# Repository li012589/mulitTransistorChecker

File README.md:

# mulitTransistorChecker
A open hardware for multi-transistor checker, that is to check a transistor is work or not

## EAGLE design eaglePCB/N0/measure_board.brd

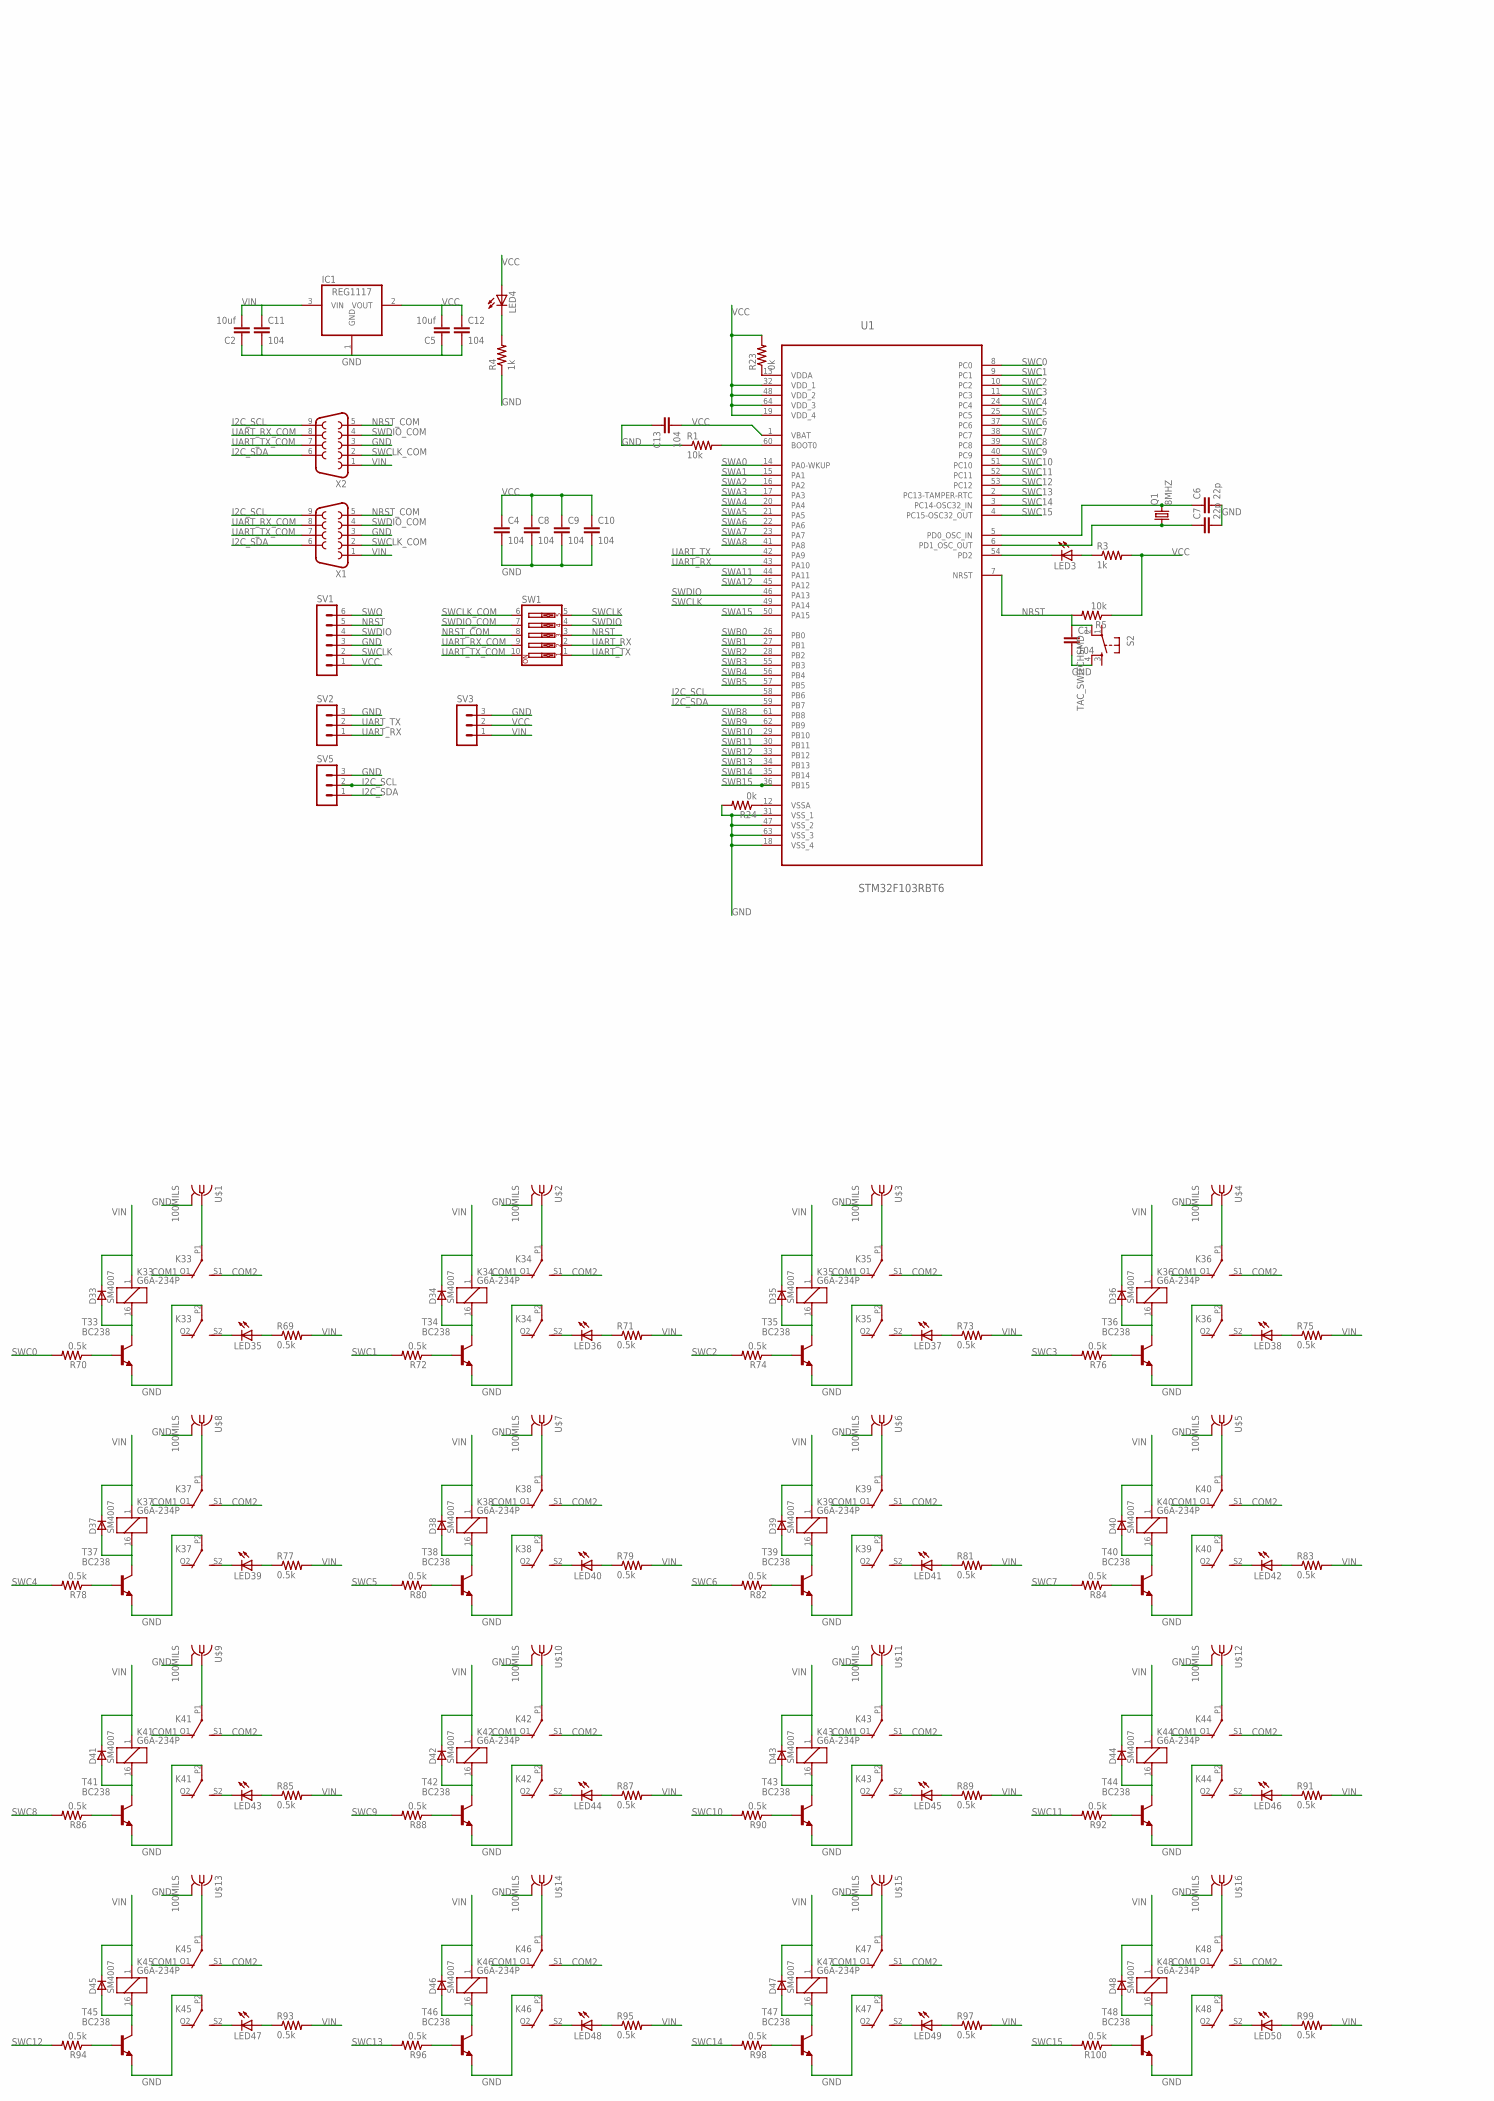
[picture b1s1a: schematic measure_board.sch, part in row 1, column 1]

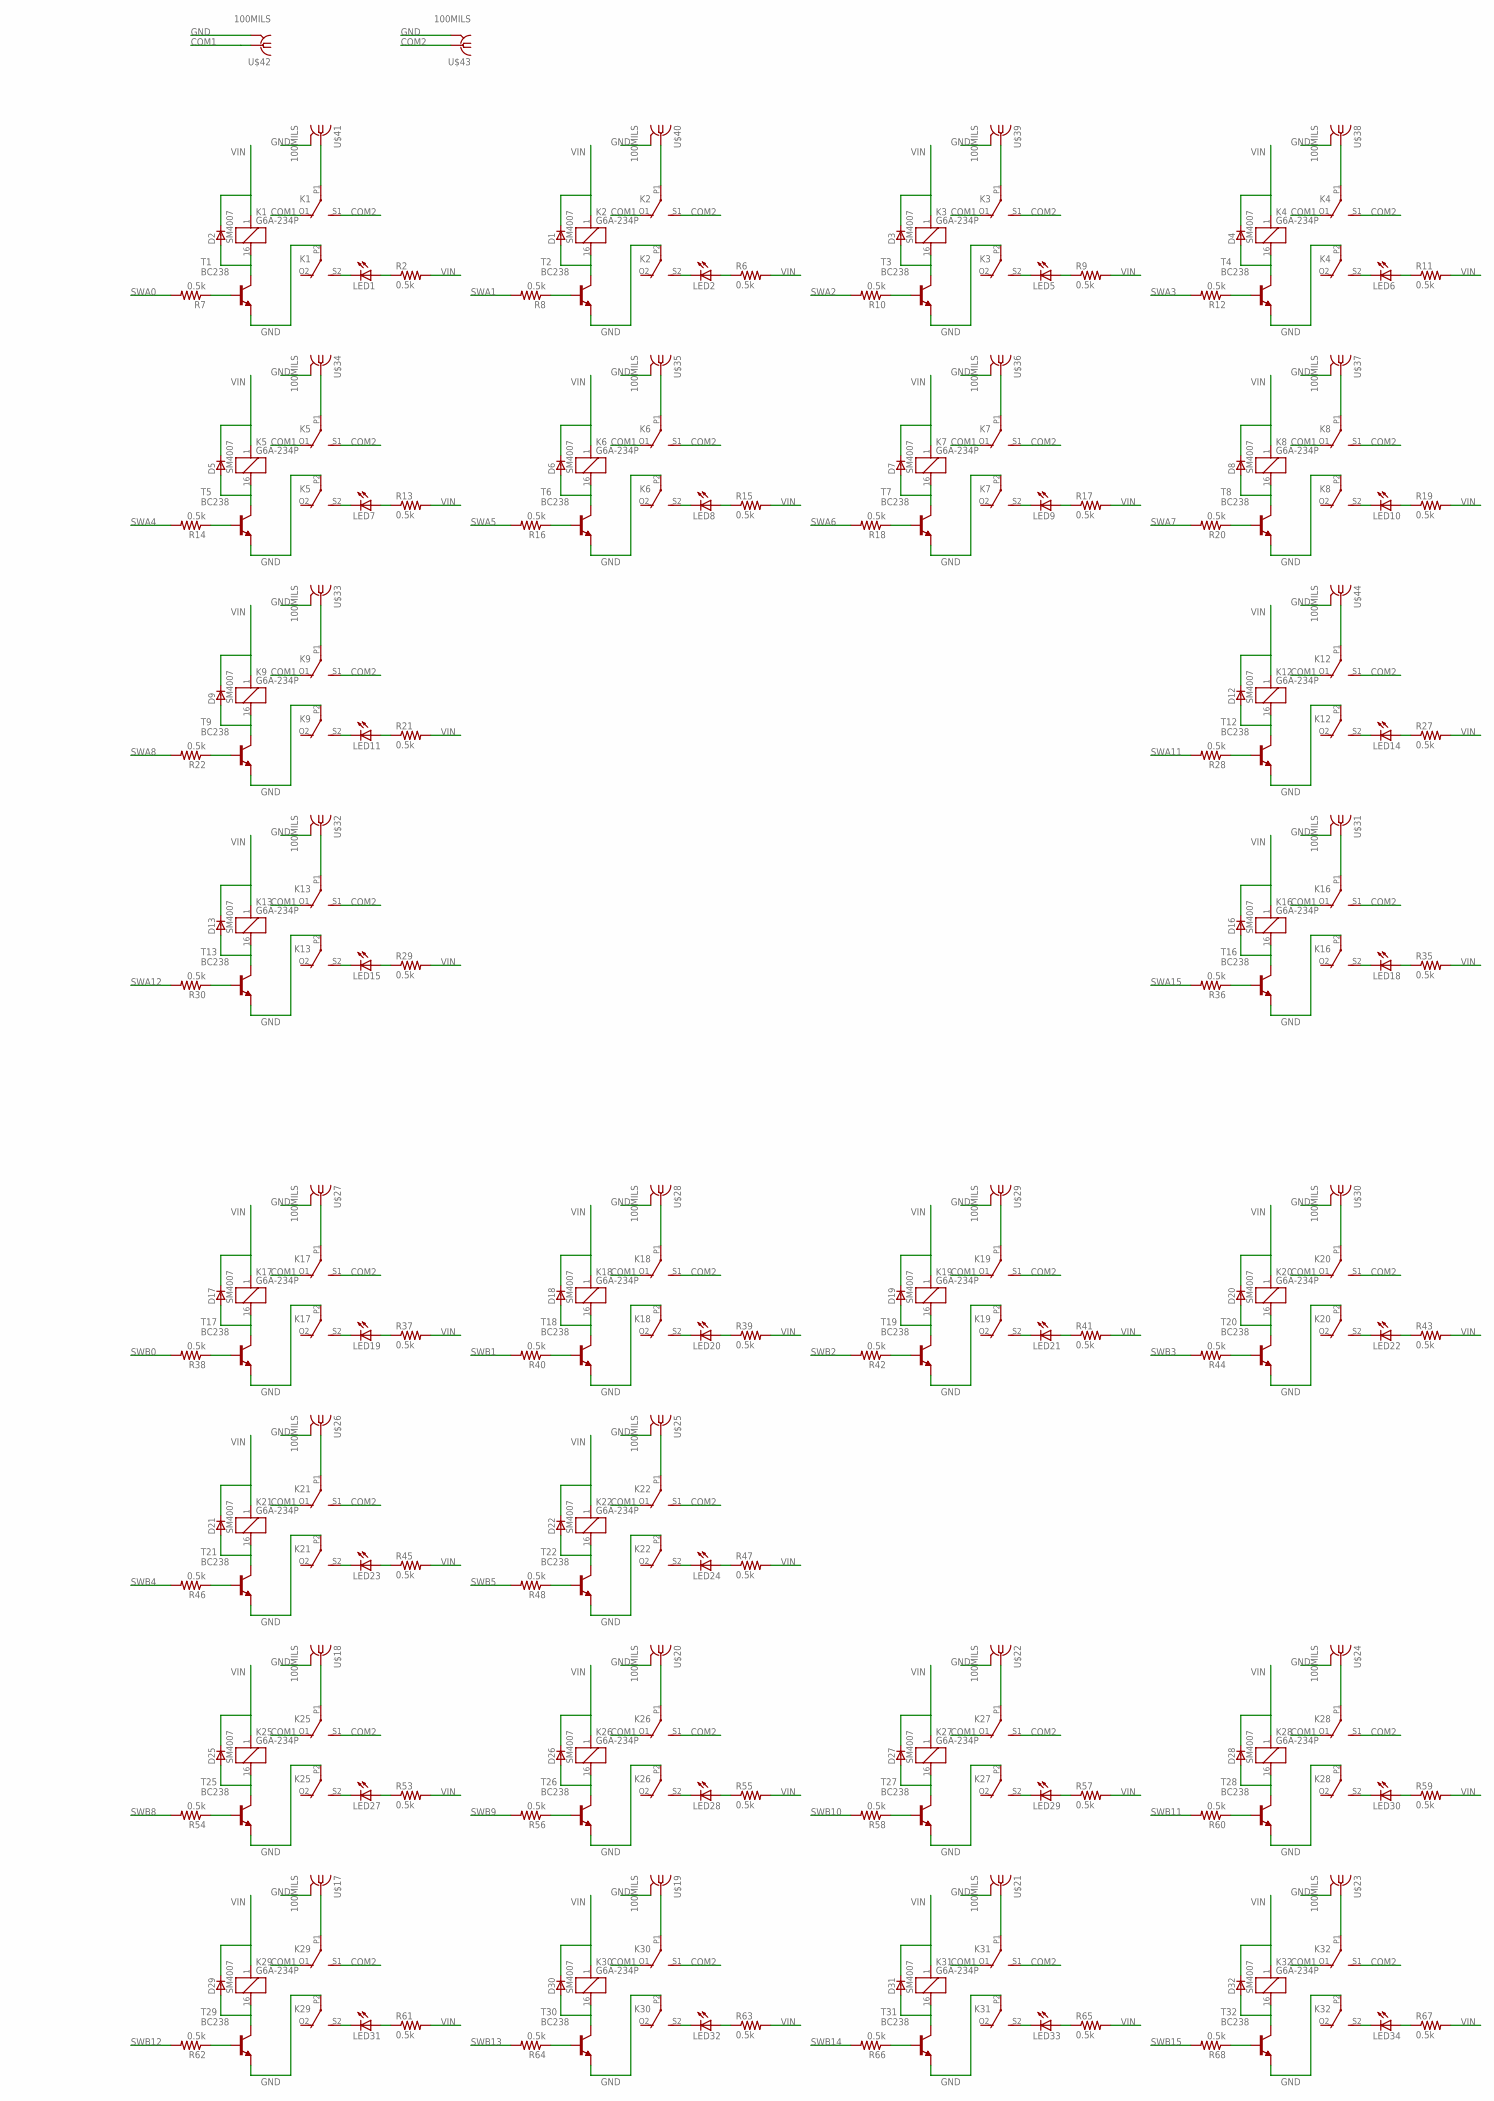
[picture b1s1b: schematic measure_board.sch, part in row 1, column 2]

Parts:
C1, C4, C8, C9, C10, C11, C12, C13: 104; C0805
C2, C5: 10uf; C1206
C6, C7: 22p; C0805
D1, D2, D3, D4, D5, D6, D7, D8, D9, D12, D13, D16, D17, D18, D19, D20, D21, D22, D25, D26, D27, D28, D29, D30, D31, D32, D33, D34, D35, D36, D37, D38, D39, D40, D41, D42, D43, D44, D45, D46, D47, D48: SM4007; MELF-MLL41_DO213AB
IC1: REG1117; SOT223
K1, K2, K3, K4, K5, K6, K7, K8, K9, K12, K13, K16, K17, K18, K19, K20, K21, K22, K25, K26, K27, K28, K29, K30, K31, K32, K33, K34, K35, K36, K37, K38, K39, K40, K41, K42, K43, K44, K45, K46, K47, K48: G6A-234P
LED1, LED2, LED5, LED6, LED7, LED8, LED9, LED10, LED11, LED14, LED15, LED18, LED19, LED20, LED21, LED22, LED23, LED24, LED27, LED28, LED29, LED30, LED31, LED32, LED33, LED34, LED35, LED36, LED37, LED38, LED39, LED40, LED41, LED42, LED43, LED44, LED45, LED46, LED47, LED48, LED49, LED50: LED3MM
LED3, LED4: LEDSML0805; SML0805
Q1: 8MHZ; HC49U70
R1, R5: 10k; M0805
R2, R6, R7, R8, R9, R10, R11, R12, R13, R14, R15, R16, R17, R18, R19, R20, R21, R22, R27, R28, R29, R30, R35, R36, R37, R38, R39, R40, R41, R42, R43, R44, R45, R46, R47, R48, R53, R54, R55, R56, R57, R58, R59, R60, R61, R62, R63, R64, R65, R66, R67, R68, R69, R70, R71, R72, R73, R74, R75, R76, R77, R78, R79, R80, R81, R82, R83, R84, R85, R86, R87, R88, R89, R90, R91, R92, R93, R94, R95, R96, R97, R98, R99, R100: 0.5k; M0805
R3, R4: 1k; M0805
R23, R24: 0k; M0805
S2: TAC_SWITCHSMD; TACTILE-SWITCH-SMD
SV1: MA06-1
SV2, SV3, SV5: MA03-1
SW1: SW_DIP-5; EDG-05
T1, T2, T3, T4, T5, T6, T7, T8, T9, T12, T13, T16, T17, T18, T19, T20, T21, T22, T25, T26, T27, T28, T29, T30, T31, T32, T33, T34, T35, T36, T37, T38, T39, T40, T41, T42, T43, T44, T45, T46, T47, T48: BC238; TO92
U1: STM32F103RBT6; QFP50P1200X1200X160-64N
U$1, U$2, U$3, U$4, U$5, U$6, U$7, U$8, U$9, U$10, U$11, U$12, U$13, U$14, U$15, U$16, U$17, U$18, U$19, U$20, U$21, U$22, U$23, U$24, U$25, U$26, U$27, U$28, U$29, U$30, U$31, U$32, U$33, U$34, U$35, U$36, U$37, U$38, U$39, U$40, U$41, U$42, U$43, U$44: 100MILS; 100MIL
X1, X2: F09HP

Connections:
COM1: K1.O1 (O), K2.O1 (O), K3.O1 (O), K4.O1 (O), K5.O1 (O), K6.O1 (O), K7.O1 (O), K8.O1 (O), K9.O1 (O), K12.O1 (O), K13.O1 (O), K16.O1 (O), K17.O1 (O), K18.O1 (O), K19.O1 (O), K20.O1 (O), K21.O1 (O), K22.O1 (O), K25.O1 (O), K26.O1 (O), K27.O1 (O), K28.O1 (O), K29.O1 (O), K30.O1 (O), K31.O1 (O), K32.O1 (O), K33.O1 (O), K34.O1 (O), K35.O1 (O), K36.O1 (O), K37.O1 (O), K38.O1 (O), K39.O1 (O), K40.O1 (O), K41.O1 (O), K42.O1 (O), K43.O1 (O), K44.O1 (O), K45.O1 (O), K46.O1 (O), K47.O1 (O), K48.O1 (O), U$42.P$1 (1)
COM2: K1.S1 (S), K2.S1 (S), K3.S1 (S), K4.S1 (S), K5.S1 (S), K6.S1 (S), K7.S1 (S), K8.S1 (S), K9.S1 (S), K12.S1 (S), K13.S1 (S), K16.S1 (S), K17.S1 (S), K18.S1 (S), K19.S1 (S), K20.S1 (S), K21.S1 (S), K22.S1 (S), K25.S1 (S), K26.S1 (S), K27.S1 (S), K28.S1 (S), K29.S1 (S), K30.S1 (S), K31.S1 (S), K32.S1 (S), K33.S1 (S), K34.S1 (S), K35.S1 (S), K36.S1 (S), K37.S1 (S), K38.S1 (S), K39.S1 (S), K40.S1 (S), K41.S1 (S), K42.S1 (S), K43.S1 (S), K44.S1 (S), K45.S1 (S), K46.S1 (S), K47.S1 (S), K48.S1 (S), U$43.P$1 (1)
GND: C1.2, C2.1, C4.2, C5.1, C6.2, C7.2, C8.2, C9.2, C10.2, C11.2, C12.2, C13.1, IC1.1 (GND), K1.P2, K2.P2, K3.P2, K4.P2, K5.P2, K6.P2, K7.P2, K8.P2, K9.P2, K12.P2, K13.P2, K16.P2, K17.P2, K18.P2, K19.P2, K20.P2, K21.P2, K22.P2, K25.P2, K26.P2, K27.P2, K28.P2, K29.P2, K30.P2, K31.P2, K32.P2, K33.P2, K34.P2, K35.P2, K36.P2, K37.P2, K38.P2, K39.P2, K40.P2, K41.P2, K42.P2, K43.P2, K44.P2, K45.P2, K46.P2, K47.P2, K48.P2, R1.1, R4.1, R24.2, S2.4, SV1.3, SV2.3, SV3.3, SV5.3, T1.1 (E), T2.1 (E), T3.1 (E), T4.1 (E), T5.1 (E), T6.1 (E), T7.1 (E), T8.1 (E), T9.1 (E), T12.1 (E), T13.1 (E), T16.1 (E), T17.1 (E), T18.1 (E), T19.1 (E), T20.1 (E), T21.1 (E), T22.1 (E), T25.1 (E), T26.1 (E), T27.1 (E), T28.1 (E), T29.1 (E), T30.1 (E), T31.1 (E), T32.1 (E), T33.1 (E), T34.1 (E), T35.1 (E), T36.1 (E), T37.1 (E), T38.1 (E), T39.1 (E), T40.1 (E), T41.1 (E), T42.1 (E), T43.1 (E), T44.1 (E), T45.1 (E), T46.1 (E), T47.1 (E), T48.1 (E), U1.18 (VSS_4), U1.31 (VSS_1), U1.47 (VSS_2), U1.63 (VSS_3), U$1.P$2 (GND), U$1.P$3 (GND), U$1.P$4 (GND), U$1.P$5 (GND), U$2.P$2 (GND), U$2.P$3 (GND), U$2.P$4 (GND), U$2.P$5 (GND), U$3.P$2 (GND), U$3.P$3 (GND), U$3.P$4 (GND), U$3.P$5 (GND), U$4.P$2 (GND), U$4.P$3 (GND), U$4.P$4 (GND), U$4.P$5 (GND), U$5.P$2 (GND), U$5.P$3 (GND), U$5.P$4 (GND), U$5.P$5 (GND), U$6.P$2 (GND), U$6.P$3 (GND), U$6.P$4 (GND), U$6.P$5 (GND), U$7.P$2 (GND), U$7.P$3 (GND), U$7.P$4 (GND), U$7.P$5 (GND), U$8.P$2 (GND), U$8.P$3 (GND), U$8.P$4 (GND), U$8.P$5 (GND), U$9.P$2 (GND), U$9.P$3 (GND), U$9.P$4 (GND), U$9.P$5 (GND), U$10.P$2 (GND), U$10.P$3 (GND), U$10.P$4 (GND), U$10.P$5 (GND), U$11.P$2 (GND), U$11.P$3 (GND), U$11.P$4 (GND), U$11.P$5 (GND), U$12.P$2 (GND), U$12.P$3 (GND), U$12.P$4 (GND), U$12.P$5 (GND), U$13.P$2 (GND), U$13.P$3 (GND), U$13.P$4 (GND), U$13.P$5 (GND), U$14.P$2 (GND), U$14.P$3 (GND), U$14.P$4 (GND), U$14.P$5 (GND), U$15.P$2 (GND), U$15.P$3 (GND), U$15.P$4 (GND), U$15.P$5 (GND), U$16.P$2 (GND), U$16.P$3 (GND), U$16.P$4 (GND), U$16.P$5 (GND), U$17.P$2 (GND), U$17.P$3 (GND), U$17.P$4 (GND), U$17.P$5 (GND), U$18.P$2 (GND), U$18.P$3 (GND), U$18.P$4 (GND), U$18.P$5 (GND), U$19.P$2 (GND), U$19.P$3 (GND), U$19.P$4 (GND), U$19.P$5 (GND), U$20.P$2 (GND), U$20.P$3 (GND), U$20.P$4 (GND), U$20.P$5 (GND), U$21.P$2 (GND), U$21.P$3 (GND), U$21.P$4 (GND), U$21.P$5 (GND), U$22.P$2 (GND), U$22.P$3 (GND), U$22.P$4 (GND), U$22.P$5 (GND), U$23.P$2 (GND), U$23.P$3 (GND), U$23.P$4 (GND), U$23.P$5 (GND), U$24.P$2 (GND), U$24.P$3 (GND), U$24.P$4 (GND), U$24.P$5 (GND), U$25.P$2 (GND), U$25.P$3 (GND), U$25.P$4 (GND), U$25.P$5 (GND), U$26.P$2 (GND), U$26.P$3 (GND), U$26.P$4 (GND), U$26.P$5 (GND), U$27.P$2 (GND), U$27.P$3 (GND), U$27.P$4 (GND), U$27.P$5 (GND), U$28.P$2 (GND), U$28.P$3 (GND), U$28.P$4 (GND), U$28.P$5 (GND), U$29.P$2 (GND), U$29.P$3 (GND), U$29.P$4 (GND), U$29.P$5 (GND), U$30.P$2 (GND), U$30.P$3 (GND), U$30.P$4 (GND), U$30.P$5 (GND), U$31.P$2 (GND), U$31.P$3 (GND), U$31.P$4 (GND), U$31.P$5 (GND), U$32.P$2 (GND), U$32.P$3 (GND), U$32.P$4 (GND), U$32.P$5 (GND), U$33.P$2 (GND), U$33.P$3 (GND), U$33.P$4 (GND), U$33.P$5 (GND), U$34.P$2 (GND), U$34.P$3 (GND), U$34.P$4 (GND), U$34.P$5 (GND), U$35.P$2 (GND), U$35.P$3 (GND), U$35.P$4 (GND), U$35.P$5 (GND), U$36.P$2 (GND), U$36.P$3 (GND), U$36.P$4 (GND), U$36.P$5 (GND), U$37.P$2 (GND), U$37.P$3 (GND), U$37.P$4 (GND), U$37.P$5 (GND), U$38.P$2 (GND), U$38.P$3 (GND), U$38.P$4 (GND), U$38.P$5 (GND), U$39.P$2 (GND), U$39.P$3 (GND), U$39.P$4 (GND), U$39.P$5 (GND), U$40.P$2 (GND), U$40.P$3 (GND), U$40.P$4 (GND), U$40.P$5 (GND), U$41.P$2 (GND), U$41.P$3 (GND), U$41.P$4 (GND), U$41.P$5 (GND), U$42.P$2 (GND), U$42.P$3 (GND), U$42.P$4 (GND), U$42.P$5 (GND), U$43.P$2 (GND), U$43.P$3 (GND), U$43.P$4 (GND), U$43.P$5 (GND), U$44.P$2 (GND), U$44.P$3 (GND), U$44.P$4 (GND), U$44.P$5 (GND), X1.3, X2.3
I2C_SCL: SV5.2, U1.58 (PB6), X1.9, X2.9
I2C_SDA: SV5.1, U1.59 (PB7), X1.6, X2.6
unnamed: LED1.A, R2.1
unnamed: C6.1, Q1.2, U1.5 (PD0_OSC_IN)
unnamed: C7.1, Q1.1, U1.6 (PD1_OSC_OUT)
unnamed: R1.2, U1.60 (BOOT0)
unnamed: K1.P1, U$41.P$1 (1)
unnamed: LED3.C, U1.54 (PD2)
unnamed: LED3.A, R3.1
unnamed: LED2.A, R6.1
unnamed: LED4.C, R4.2
unnamed: D1.A, K2.16 (2), T2.3 (C)
unnamed: K1.S2 (S), LED1.K (C)
unnamed: R8.1, T2.2 (B)
unnamed: D2.A, K1.16 (2), T1.3 (C)
unnamed: K2.S2 (S), LED2.K (C)
unnamed: K2.P1, U$40.P$1 (1)
unnamed: LED5.A, R9.1
unnamed: D3.A, K3.16 (2), T3.3 (C)
unnamed: R7.1, T1.2 (B)
unnamed: R10.1, T3.2 (B)
unnamed: K3.S2 (S), LED5.K (C)
unnamed: K3.P1, U$39.P$1 (1)
unnamed: LED6.A, R11.1
unnamed: D4.A, K4.16 (2), T4.3 (C)
unnamed: R12.1, T4.2 (B)
unnamed: K4.S2 (S), LED6.K (C)
unnamed: K4.P1, U$38.P$1 (1)
unnamed: LED7.A, R13.1
unnamed: D5.A, K5.16 (2), T5.3 (C)
unnamed: R14.1, T5.2 (B)
unnamed: K5.S2 (S), LED7.K (C)
unnamed: K5.P1, U$34.P$1 (1)
unnamed: LED8.A, R15.1
unnamed: D6.A, K6.16 (2), T6.3 (C)
unnamed: R16.1, T6.2 (B)
unnamed: K6.S2 (S), LED8.K (C)
unnamed: K6.P1, U$35.P$1 (1)
unnamed: LED9.A, R17.1
unnamed: D7.A, K7.16 (2), T7.3 (C)
unnamed: R18.1, T7.2 (B)
unnamed: K7.S2 (S), LED9.K (C)
unnamed: K7.P1, U$36.P$1 (1)
unnamed: LED10.A, R19.1
unnamed: D8.A, K8.16 (2), T8.3 (C)
unnamed: R20.1, T8.2 (B)
unnamed: K8.S2 (S), LED10.K (C)
unnamed: K8.P1, U$37.P$1 (1)
unnamed: LED11.A, R21.1
unnamed: D9.A, K9.16 (2), T9.3 (C)
unnamed: R22.1, T9.2 (B)
unnamed: K9.S2 (S), LED11.K (C)
unnamed: K9.P1, U$33.P$1 (1)
unnamed: R23.1, U1.13 (VDDA)
unnamed: R24.1, U1.12 (VSSA)
unnamed: LED14.A, R27.1
unnamed: D12.A, K12.16 (2), T12.3 (C)
unnamed: R28.1, T12.2 (B)
unnamed: K12.S2 (S), LED14.K (C)
unnamed: K12.P1, U$44.P$1 (1)
unnamed: LED15.A, R29.1
unnamed: D13.A, K13.16 (2), T13.3 (C)
unnamed: R30.1, T13.2 (B)
unnamed: K13.S2 (S), LED15.K (C)
unnamed: K13.P1, U$32.P$1 (1)
unnamed: LED18.A, R35.1
unnamed: D16.A, K16.16 (2), T16.3 (C)
unnamed: R36.1, T16.2 (B)
unnamed: K16.S2 (S), LED18.K (C)
unnamed: K16.P1, U$31.P$1 (1)
unnamed: LED19.A, R37.1
unnamed: D17.A, K17.16 (2), T17.3 (C)
unnamed: R38.1, T17.2 (B)
unnamed: K17.S2 (S), LED19.K (C)
unnamed: K17.P1, U$27.P$1 (1)
unnamed: LED20.A, R39.1
unnamed: D18.A, K18.16 (2), T18.3 (C)
unnamed: R40.1, T18.2 (B)
unnamed: K18.S2 (S), LED20.K (C)
unnamed: K18.P1, U$28.P$1 (1)
unnamed: LED21.A, R41.1
unnamed: D19.A, K19.16 (2), T19.3 (C)
unnamed: R42.1, T19.2 (B)
unnamed: K19.S2 (S), LED21.K (C)
unnamed: K19.P1, U$29.P$1 (1)
unnamed: LED22.A, R43.1
unnamed: D20.A, K20.16 (2), T20.3 (C)
unnamed: R44.1, T20.2 (B)
unnamed: K20.S2 (S), LED22.K (C)
unnamed: K20.P1, U$30.P$1 (1)
unnamed: LED23.A, R45.1
unnamed: D21.A, K21.16 (2), T21.3 (C)
unnamed: R46.1, T21.2 (B)
unnamed: K21.S2 (S), LED23.K (C)
unnamed: K21.P1, U$26.P$1 (1)
unnamed: LED24.A, R47.1
unnamed: D22.A, K22.16 (2), T22.3 (C)
unnamed: R48.1, T22.2 (B)
unnamed: K22.S2 (S), LED24.K (C)
unnamed: K22.P1, U$25.P$1 (1)
unnamed: LED27.A, R53.1
unnamed: D25.A, K25.16 (2), T25.3 (C)
unnamed: R54.1, T25.2 (B)
unnamed: K25.S2 (S), LED27.K (C)
unnamed: K25.P1, U$18.P$1 (1)
unnamed: LED28.A, R55.1
unnamed: D26.A, K26.16 (2), T26.3 (C)
unnamed: R56.1, T26.2 (B)
unnamed: K26.S2 (S), LED28.K (C)
unnamed: K26.P1, U$20.P$1 (1)
unnamed: LED29.A, R57.1
unnamed: D27.A, K27.16 (2), T27.3 (C)
unnamed: R58.1, T27.2 (B)
unnamed: K27.S2 (S), LED29.K (C)
unnamed: K27.P1, U$22.P$1 (1)
unnamed: LED30.A, R59.1
unnamed: D28.A, K28.16 (2), T28.3 (C)
unnamed: R60.1, T28.2 (B)
unnamed: K28.S2 (S), LED30.K (C)
unnamed: K28.P1, U$24.P$1 (1)
unnamed: LED31.A, R61.1
unnamed: D29.A, K29.16 (2), T29.3 (C)
unnamed: R62.1, T29.2 (B)
unnamed: K29.S2 (S), LED31.K (C)
unnamed: K29.P1, U$17.P$1 (1)
unnamed: LED32.A, R63.1
unnamed: D30.A, K30.16 (2), T30.3 (C)
unnamed: R64.1, T30.2 (B)
unnamed: K30.S2 (S), LED32.K (C)
unnamed: K30.P1, U$19.P$1 (1)
unnamed: LED33.A, R65.1
unnamed: D31.A, K31.16 (2), T31.3 (C)
unnamed: R66.1, T31.2 (B)
unnamed: K31.S2 (S), LED33.K (C)
unnamed: K31.P1, U$21.P$1 (1)
unnamed: LED34.A, R67.1
unnamed: D32.A, K32.16 (2), T32.3 (C)
unnamed: R68.1, T32.2 (B)
unnamed: K32.S2 (S), LED34.K (C)
unnamed: K32.P1, U$23.P$1 (1)
unnamed: LED35.A, R69.1
unnamed: D33.A, K33.16 (2), T33.3 (C)
unnamed: R70.1, T33.2 (B)
unnamed: K33.S2 (S), LED35.K (C)
unnamed: K33.P1, U$1.P$1 (1)
unnamed: LED36.A, R71.1
unnamed: D34.A, K34.16 (2), T34.3 (C)
unnamed: R72.1, T34.2 (B)
unnamed: K34.S2 (S), LED36.K (C)
unnamed: K34.P1, U$2.P$1 (1)
unnamed: LED37.A, R73.1
unnamed: D35.A, K35.16 (2), T35.3 (C)
unnamed: R74.1, T35.2 (B)
unnamed: K35.S2 (S), LED37.K (C)
unnamed: K35.P1, U$3.P$1 (1)
unnamed: LED38.A, R75.1
unnamed: D36.A, K36.16 (2), T36.3 (C)
unnamed: R76.1, T36.2 (B)
unnamed: K36.S2 (S), LED38.K (C)
unnamed: K36.P1, U$4.P$1 (1)
unnamed: LED39.A, R77.1
unnamed: D37.A, K37.16 (2), T37.3 (C)
unnamed: R78.1, T37.2 (B)
unnamed: K37.S2 (S), LED39.K (C)
unnamed: K37.P1, U$8.P$1 (1)
unnamed: LED40.A, R79.1
unnamed: D38.A, K38.16 (2), T38.3 (C)
unnamed: R80.1, T38.2 (B)
unnamed: K38.S2 (S), LED40.K (C)
unnamed: K38.P1, U$7.P$1 (1)
unnamed: LED41.A, R81.1
unnamed: D39.A, K39.16 (2), T39.3 (C)
unnamed: R82.1, T39.2 (B)
unnamed: K39.S2 (S), LED41.K (C)
unnamed: K39.P1, U$6.P$1 (1)
unnamed: LED42.A, R83.1
unnamed: D40.A, K40.16 (2), T40.3 (C)
unnamed: R84.1, T40.2 (B)
unnamed: K40.S2 (S), LED42.K (C)
unnamed: K40.P1, U$5.P$1 (1)
unnamed: LED43.A, R85.1
unnamed: D41.A, K41.16 (2), T41.3 (C)
unnamed: R86.1, T41.2 (B)
unnamed: K41.S2 (S), LED43.K (C)
unnamed: K41.P1, U$9.P$1 (1)
unnamed: LED44.A, R87.1
unnamed: D42.A, K42.16 (2), T42.3 (C)
unnamed: R88.1, T42.2 (B)
unnamed: K42.S2 (S), LED44.K (C)
unnamed: K42.P1, U$10.P$1 (1)
unnamed: LED45.A, R89.1
unnamed: D43.A, K43.16 (2), T43.3 (C)
unnamed: R90.1, T43.2 (B)
unnamed: K43.S2 (S), LED45.K (C)
unnamed: K43.P1, U$11.P$1 (1)
unnamed: LED46.A, R91.1
unnamed: D44.A, K44.16 (2), T44.3 (C)
unnamed: R92.1, T44.2 (B)
unnamed: K44.S2 (S), LED46.K (C)
unnamed: K44.P1, U$12.P$1 (1)
unnamed: LED47.A, R93.1
unnamed: D45.A, K45.16 (2), T45.3 (C)
unnamed: R94.1, T45.2 (B)
unnamed: K45.S2 (S), LED47.K (C)
unnamed: K45.P1, U$13.P$1 (1)
unnamed: LED48.A, R95.1
unnamed: D46.A, K46.16 (2), T46.3 (C)
unnamed: R96.1, T46.2 (B)
unnamed: K46.S2 (S), LED48.K (C)
unnamed: K46.P1, U$14.P$1 (1)
unnamed: LED49.A, R97.1
unnamed: D47.A, K47.16 (2), T47.3 (C)
unnamed: R98.1, T47.2 (B)
unnamed: K47.S2 (S), LED49.K (C)
unnamed: K47.P1, U$15.P$1 (1)
unnamed: LED50.A, R99.1
unnamed: D48.A, K48.16 (2), T48.3 (C)
unnamed: R100.1, T48.2 (B)
unnamed: K48.S2 (S), LED50.K (C)
unnamed: K48.P1, U$16.P$1 (1)
NRST: C1.1, R5.2, S2.2, SV1.5, SW1.3, U1.7 (NRST)
NRST_COM: SW1.8, X1.5, X2.5
SWA0: R7.2, U1.14 (PA0-WKUP)
SWA1: R8.2, U1.15 (PA1)
SWA2: R10.2, U1.16 (PA2)
SWA3: R12.2, U1.17 (PA3)
SWA4: R14.2, U1.20 (PA4)
SWA5: R16.2, U1.21 (PA5)
SWA6: R18.2, U1.22 (PA6)
SWA7: R20.2, U1.23 (PA7)
SWA8: R22.2, U1.41 (PA8)
SWA11: R28.2, U1.44 (PA11)
SWA12: R30.2, U1.45 (PA12)
SWA15: R36.2, U1.50 (PA15)
SWB0: R38.2, U1.26 (PB0)
SWB1: R40.2, U1.27 (PB1)
SWB2: R42.2, U1.28 (PB2)
SWB3: R44.2, U1.55 (PB3)
SWB4: R46.2, U1.56 (PB4)
SWB5: R48.2, U1.57 (PB5)
SWB8: R54.2, U1.61 (PB8)
SWB9: R56.2, U1.62 (PB9)
SWB10: R58.2, U1.29 (PB10)
SWB11: R60.2, U1.30 (PB11)
SWB12: R62.2, U1.33 (PB12)
SWB13: R64.2, U1.34 (PB13)
SWB14: R66.2, U1.35 (PB14)
SWB15: R68.2, U1.36 (PB15)
SWC0: R70.2, U1.8 (PC0)
SWC1: R72.2, U1.9 (PC1)
SWC2: R74.2, U1.10 (PC2)
SWC3: R76.2, U1.11 (PC3)
SWC4: R78.2, U1.24 (PC4)
SWC5: R80.2, U1.25 (PC5)
SWC6: R82.2, U1.37 (PC6)
SWC7: R84.2, U1.38 (PC7)
SWC8: R86.2, U1.39 (PC8)
SWC9: R88.2, U1.40 (PC9)
SWC10: R90.2, U1.51 (PC10)
SWC11: R92.2, U1.52 (PC11)
SWC12: R94.2, U1.53 (PC12)
SWC13: R96.2, U1.2 (PC13-TAMPER-RTC)
SWC14: R98.2, U1.3 (PC14-OSC32_IN)
SWC15: R100.2, U1.4 (PC15-OSC32_OUT)
SWCLK: SV1.2, SW1.5, U1.49 (PA14)
SWCLK_COM: SW1.6, X1.2, X2.2
SWDIO: SV1.4, SW1.4, U1.46 (PA13)
SWDIO_COM: SW1.7, X1.4, X2.4
SWO: SV1.6
UART_RX: SV2.1, SW1.2, U1.43 (PA10)
UART_RX_COM: SW1.9, X1.8, X2.8
UART_TX: SV2.2, SW1.1, U1.42 (PA9)
UART_TX_COM: SW1.10, X1.7, X2.7
VCC: C4.1, C5.2, C8.1, C9.1, C10.1, C12.1, C13.2, IC1.2 (VOUT), LED4.A, R3.2, R5.1, R23.2, SV1.1, SV3.2, U1.1 (VBAT), U1.19 (VDD_4), U1.32 (VDD_1), U1.48 (VDD_2), U1.64 (VDD_3)
VIN: C2.2, C11.1, D1.C, D2.C, D3.C, D4.C, D5.C, D6.C, D7.C, D8.C, D9.C, D12.C, D13.C, D16.C, D17.C, D18.C, D19.C, D20.C, D21.C, D22.C, D25.C, D26.C, D27.C, D28.C, D29.C, D30.C, D31.C, D32.C, D33.C, D34.C, D35.C, D36.C, D37.C, D38.C, D39.C, D40.C, D41.C, D42.C, D43.C, D44.C, D45.C, D46.C, D47.C, D48.C, IC1.3 (VIN), K1.1, K2.1, K3.1, K4.1, K5.1, K6.1, K7.1, K8.1, K9.1, K12.1, K13.1, K16.1, K17.1, K18.1, K19.1, K20.1, K21.1, K22.1, K25.1, K26.1, K27.1, K28.1, K29.1, K30.1, K31.1, K32.1, K33.1, K34.1, K35.1, K36.1, K37.1, K38.1, K39.1, K40.1, K41.1, K42.1, K43.1, K44.1, K45.1, K46.1, K47.1, K48.1, R2.2, R6.2, R9.2, R11.2, R13.2, R15.2, R17.2, R19.2, R21.2, R27.2, R29.2, R35.2, R37.2, R39.2, R41.2, R43.2, R45.2, R47.2, R53.2, R55.2, R57.2, R59.2, R61.2, R63.2, R65.2, R67.2, R69.2, R71.2, R73.2, R75.2, R77.2, R79.2, R81.2, R83.2, R85.2, R87.2, R89.2, R91.2, R93.2, R95.2, R97.2, R99.2, SV3.1, X1.1, X2.1

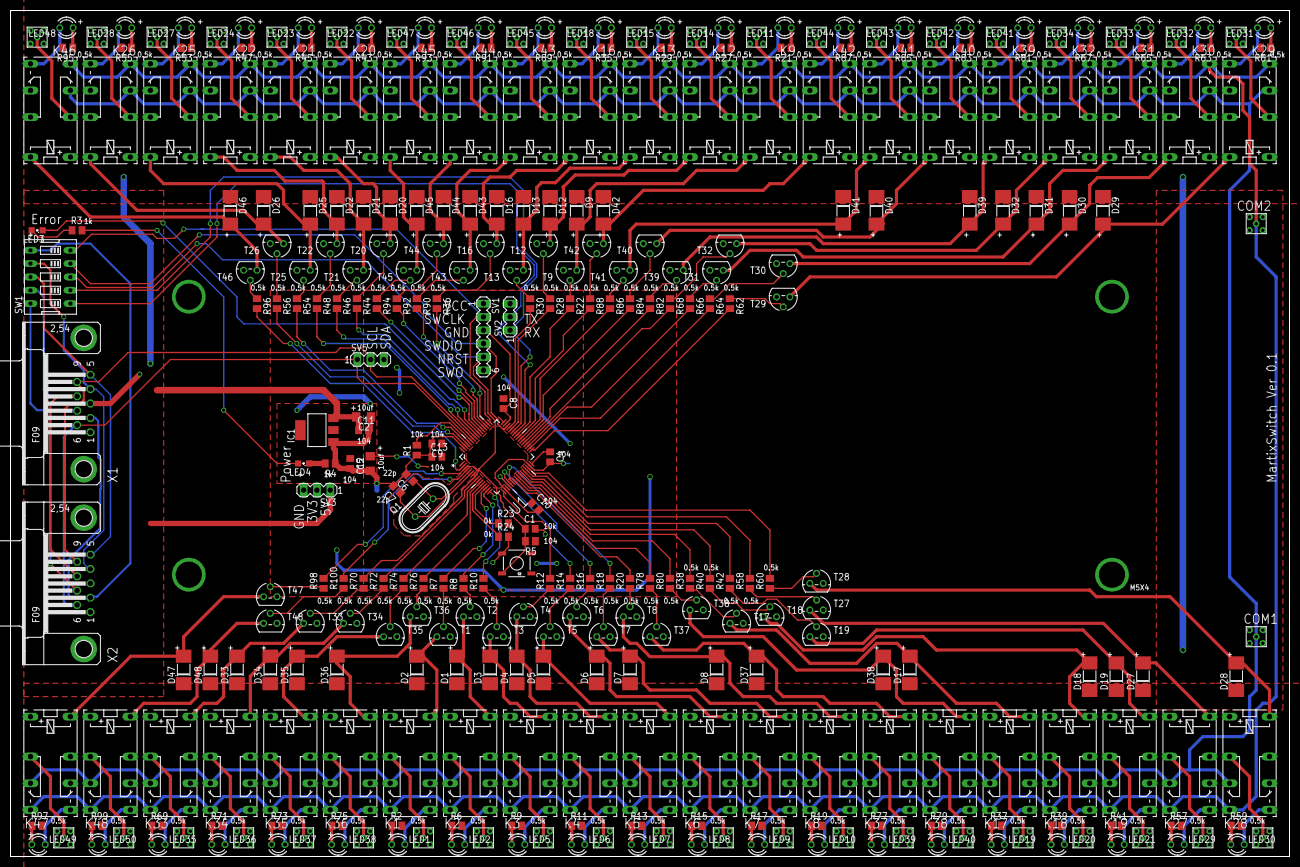
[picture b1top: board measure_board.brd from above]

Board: 2 copper layers, 243.8 x 161.3 mm, 327 parts (0 on the bottom side), 277 nets.

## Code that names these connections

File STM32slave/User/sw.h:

#ifndef _SW_H
#define _SW_H

#include "stm32f10x.h"

#define ON 1
#define OFF 0

#define SWA0(a) if (a) \
	GPIO_SetBits(GPIOA,GPIO_Pin_0);\
	else	\
	GPIO_ResetBits(GPIOA,GPIO_Pin_0)
#define SWA1(a) if (a) \
	GPIO_SetBits(GPIOA,GPIO_Pin_1);\
	else	\
	GPIO_ResetBits(GPIOA,GPIO_Pin_1)
#define SWA2(a) if (a) \
	GPIO_SetBits(GPIOA,GPIO_Pin_2);\
	else	\
	GPIO_ResetBits(GPIOA,GPIO_Pin_2)
#define SWA3(a) if (a) \
	GPIO_SetBits(GPIOA,GPIO_Pin_3);\
	else	\
	GPIO_ResetBits(GPIOA,GPIO_Pin_3)
#define SWA4(a) if (a) \
	GPIO_SetBits(GPIOA,GPIO_Pin_4);\
	else	\
	GPIO_ResetBits(GPIOA,GPIO_Pin_4)
#define SWA5(a) if (a) \
	GPIO_SetBits(GPIOA,GPIO_Pin_5);\
	else	\
	GPIO_ResetBits(GPIOA,GPIO_Pin_5)
#define SWA6(a) if (a) \
	GPIO_SetBits(GPIOA,GPIO_Pin_6);\
	else	\
	GPIO_ResetBits(GPIOA,GPIO_Pin_6)
#define SWA7(a) if (a) \
	GPIO_SetBits(GPIOA,GPIO_Pin_7);\
	else	\
	GPIO_ResetBits(GPIOA,GPIO_Pin_7)
#define SWA8(a) if (a) \
	GPIO_SetBits(GPIOA,GPIO_Pin_8);\
	else	\
	GPIO_ResetBits(GPIOA,GPIO_Pin_8)
#define SWA11(a) if (a) \
	GPIO_SetBits(GPIOA,GPIO_Pin_11);\
	else	\
	GPIO_ResetBits(GPIOA,GPIO_Pin_11)
#define SWA12(a) if (a) \
	GPIO_SetBits(GPIOA,GPIO_Pin_12);\
	else	\
	GPIO_ResetBits(GPIOA,GPIO_Pin_12)
#define SWA15(a) if (a) \
	GPIO_SetBits(GPIOA,GPIO_Pin_15);\
	else	\
	GPIO_ResetBits(GPIOA,GPIO_Pin_15)
	
#define SWB0(a) if (a) \
	GPIO_SetBits(GPIOB,GPIO_Pin_0);\
	else	\
	GPIO_ResetBits(GPIOB,GPIO_Pin_0)
#define SWB1(a) if (a) \
	GPIO_SetBits(GPIOB,GPIO_Pin_1);\
	else	\
	GPIO_ResetBits(GPIOB,GPIO_Pin_1)
#define SWB2(a) if (a) \
	GPIO_SetBits(GPIOB,GPIO_Pin_2);\
	else	\
	GPIO_ResetBits(GPIOB,GPIO_Pin_2)
#define SWB3(a) if (a) \
	GPIO_SetBits(GPIOB,GPIO_Pin_3);\
	else	\
	GPIO_ResetBits(GPIOB,GPIO_Pin_3)
#define SWB4(a) if (a) \
	GPIO_SetBits(GPIOB,GPIO_Pin_4);\
	else	\
	GPIO_ResetBits(GPIOB,GPIO_Pin_4)
#define SWB5(a) if (a) \
	GPIO_SetBits(GPIOB,GPIO_Pin_5);\
	else	\
	GPIO_ResetBits(GPIOB,GPIO_Pin_5)
#define SWB8(a) if (a) \
	GPIO_SetBits(GPIOB,GPIO_Pin_8);\
	else	\
	GPIO_ResetBits(GPIOB,GPIO_Pin_8)
#define SWB9(a) if (a) \
	GPIO_SetBits(GPIOB,GPIO_Pin_9);\
	else	\
	GPIO_ResetBits(GPIOB,GPIO_Pin_9)
#define SWB10(a) if (a) \
	GPIO_SetBits(GPIOB,GPIO_Pin_10);\
	else	\
	GPIO_ResetBits(GPIOB,GPIO_Pin_10)
#define SWB11(a) if (a) \
	GPIO_SetBits(GPIOB,GPIO_Pin_11);\
	else	\
	GPIO_ResetBits(GPIOB,GPIO_Pin_11)
#define SWB12(a) if (a) \
	GPIO_SetBits(GPIOB,GPIO_Pin_12);\
	else	\
	GPIO_ResetBits(GPIOB,GPIO_Pin_12)
#define SWB13(a) if (a) \
	GPIO_SetBits(GPIOB,GPIO_Pin_13);\
	else	\
	GPIO_ResetBits(GPIOB,GPIO_Pin_13)
#define SWB14(a) if (a) \
	GPIO_SetBits(GPIOB,GPIO_Pin_14);\
	else	\
	GPIO_ResetBits(GPIOB,GPIO_Pin_14)
#define SWB15(a) if (a) \
	GPIO_SetBits(GPIOB,GPIO_Pin_15);\
	else	\
	GPIO_ResetBits(GPIOB,GPIO_Pin_15)

#define SWC0(a) if (a) \
	GPIO_SetBits(GPIOC,GPIO_Pin_0);\
	else	\
	GPIO_ResetBits(GPIOC,GPIO_Pin_0)
#define SWC1(a) if (a) \
	GPIO_SetBits(GPIOC,GPIO_Pin_1);\
	else	\
	GPIO_ResetBits(GPIOC,GPIO_Pin_1)
#define SWC2(a) if (a) \
	GPIO_SetBits(GPIOC,GPIO_Pin_2);\
	else	\
	GPIO_ResetBits(GPIOC,GPIO_Pin_2)
#define SWC3(a) if (a) \
	GPIO_SetBits(GPIOC,GPIO_Pin_3);\
	else	\
	GPIO_ResetBits(GPIOC,GPIO_Pin_3)
#define SWC4(a) if (a) \
	GPIO_SetBits(GPIOC,GPIO_Pin_4);\
	else	\
	GPIO_ResetBits(GPIOC,GPIO_Pin_4)
#define SWC5(a) if (a) \
	GPIO_SetBits(GPIOC,GPIO_Pin_5);\
	else	\
	GPIO_ResetBits(GPIOC,GPIO_Pin_5)
#define SWC6(a) if (a) \
	GPIO_SetBits(GPIOC,GPIO_Pin_6);\
	else	\
	GPIO_ResetBits(GPIOC,GPIO_Pin_6)
#define SWC7(a) if (a) \
	GPIO_SetBits(GPIOC,GPIO_Pin_7);\
	else	\
	GPIO_ResetBits(GPIOC,GPIO_Pin_7)
#define SWC8(a) if (a) \
	GPIO_SetBits(GPIOC,GPIO_Pin_8);\
	else	\
	GPIO_ResetBits(GPIOC,GPIO_Pin_8)
#define SWC9(a) if (a) \
	GPIO_SetBits(GPIOC,GPIO_Pin_9);\
	else	\
	GPIO_ResetBits(GPIOC,GPIO_Pin_9)
#define SWC10(a) if (a) \
	GPIO_SetBits(GPIOC,GPIO_Pin_10);\
	else	\
	GPIO_ResetBits(GPIOC,GPIO_Pin_10)
#define SWC11(a) if (a) \
	GPIO_SetBits(GPIOC,GPIO_Pin_11);\
	else	\
	GPIO_ResetBits(GPIOC,GPIO_Pin_11)
#define SWC12(a) if (a) \
	GPIO_SetBits(GPIOC,GPIO_Pin_12);\
	else	\
	GPIO_ResetBits(GPIOC,GPIO_Pin_12)
#define SWC13(a) if (a) \
	GPIO_SetBits(GPIOC,GPIO_Pin_13);\
	else	\
	GPIO_ResetBits(GPIOC,GPIO_Pin_13)
#define SWC14(a) if (a) \
	GPIO_SetBits(GPIOC,GPIO_Pin_14);\
	else	\
	GPIO_ResetBits(GPIOC,GPIO_Pin_14)
#define SWC15(a) if (a) \
	GPIO_SetBits(GPIOC,GPIO_Pin_15);\
	else	\
	GPIO_ResetBits(GPIOC,GPIO_Pin_15)
	
#define SWD2(a) if (a) \
	GPIO_SetBits(GPIOD,GPIO_Pin_2);\
	else	\
	GPIO_ResetBits(GPIOD,GPIO_Pin_2)

void SW_GPIO_Con(void);

#endif /*_led_h*/

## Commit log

2017-04-05 add all used datasheets
2017-04-05 add measure board PCB(slave)
2017-04-05 add convert tool(.cam file)
2017-04-05 establish a project
2017-04-05 finish slave program
2017-04-05 add readme files

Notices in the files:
parts and their libraries:
SparkFun-Retired: Licensing:Creative Commons ShareAlike 4.0 International - https://creativecommons.org/licenses/by-sa/4.0
